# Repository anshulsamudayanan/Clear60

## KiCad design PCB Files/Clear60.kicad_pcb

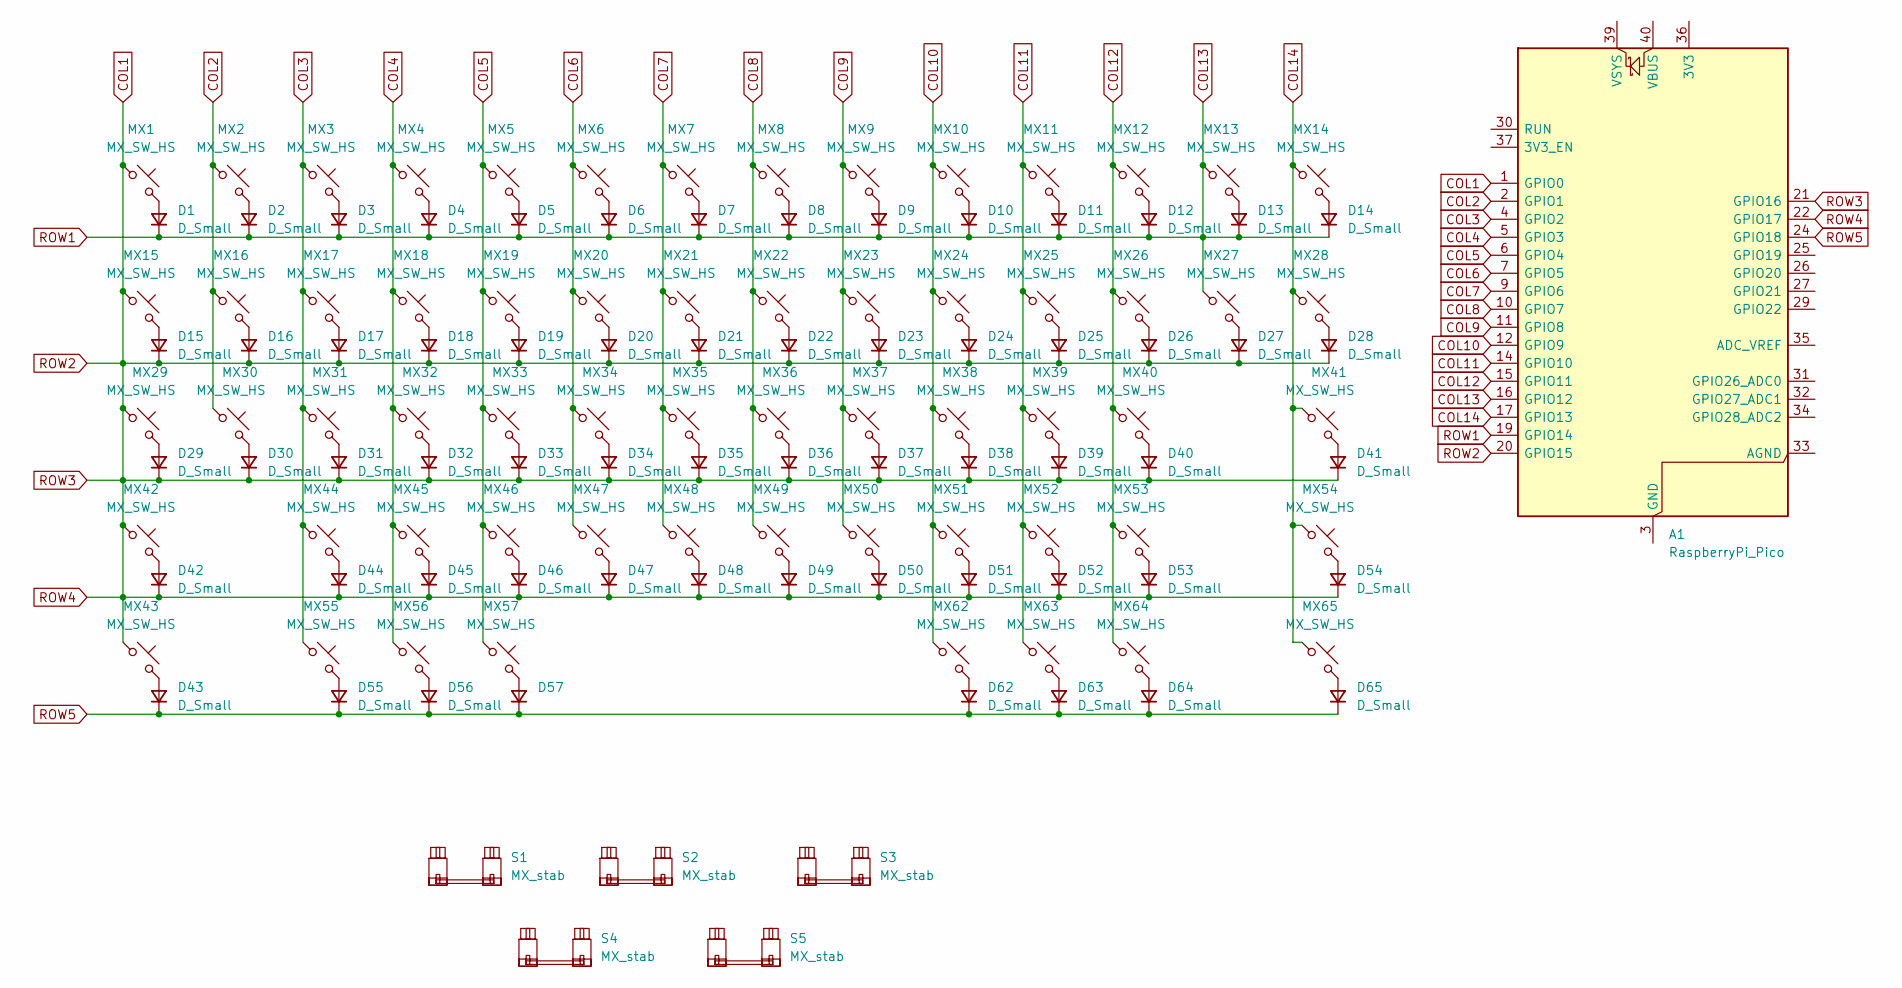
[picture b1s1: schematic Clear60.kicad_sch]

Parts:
A1: RaspberryPi_Pico; RaspberryPi_Pico_Common_Unspecified
D1, D2, D3, D4, D5, D6, D7, D8, D9, D10, D11, D12, D13, D14, D15, D16, D17, D18, D19, D20, D21, D22, D23, D24, D25, D26, D27, D28, D29, D30, D31, D32, D33, D34, D35, D36, D37, D38, D39, D40, D41, D42, D43, D44, D45, D46, D47, D48, D49, D50, D51, D52, D53, D54, D55, D56, D57, D62, D63, D64, D65: D_Small; D_SOD-123
MX1, MX2, MX3, MX4, MX5, MX6, MX7, MX8, MX9, MX10, MX11, MX12, MX13, MX14, MX16, MX17, MX18, MX19, MX20, MX21, MX22, MX23, MX24, MX25, MX26, MX27, MX30, MX31, MX32, MX33, MX34, MX35, MX36, MX37, MX38, MX39, MX40, MX41, MX42, MX44, MX45, MX46, MX47, MX48, MX49, MX50, MX51, MX52, MX53, MX54, MX57: MX_SW_HS; SW_MX_HS_CPG151101S11_1u
MX15, MX28: MX_SW_HS; SW_MX_HS_CPG151101S11_1.5u
MX29: MX_SW_HS; SW_MX_HS_CPG151101S11_1.75u
MX43, MX55, MX56, MX62, MX63, MX64, MX65: MX_SW_HS; SW_MX_HS_CPG151101S11_1.25u
S1, S3: MX_stab; STAB_MX_P_2.25u
S2: MX_stab; STAB_MX_P_2u
S4: MX_stab; STAB_MX_P_2.75u
S5: MX_stab; STAB_MX_P_6.25u

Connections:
COL1: A1.1 (GPIO0), A1.20 (GPIO15), A1.21 (GPIO16), A1.22 (GPIO17), D15.1 (K), D16.1 (K), D17.1 (K), D18.1 (K), D19.1 (K), D20.1 (K), D21.1 (K), D22.1 (K), D23.1 (K), D24.1 (K), D25.1 (K), D26.1 (K), D27.1 (K), D28.1 (K), D29.1 (K), D30.1 (K), D31.1 (K), D32.1 (K), D33.1 (K), D34.1 (K), D35.1 (K), D36.1 (K), D37.1 (K), D38.1 (K), D39.1 (K), D40.1 (K), D41.1 (K), D42.1 (K), D44.1 (K), D45.1 (K), D46.1 (K), D47.1 (K), D48.1 (K), D49.1 (K), D50.1 (K), D51.1 (K), D52.1 (K), D53.1 (K), D54.1 (K), MX1.1, MX15.1, MX29.1, MX42.1, MX43.1
COL2: A1.2 (GPIO1), MX2.1, MX16.1, MX30.1
COL3: A1.4 (GPIO2), MX3.1, MX17.1, MX31.1, MX44.1, MX55.1
COL4: A1.5 (GPIO3), MX4.1, MX18.1, MX32.1, MX45.1, MX56.1
COL5: A1.6 (GPIO4), MX5.1, MX19.1, MX33.1, MX46.1, MX57.1
COL6: A1.7 (GPIO5), MX6.1, MX20.1, MX34.1, MX47.1
COL7: A1.9 (GPIO6), MX7.1, MX21.1, MX35.1, MX48.1
COL8: A1.10 (GPIO7), MX8.1, MX22.1, MX36.1, MX49.1
COL9: A1.11 (GPIO8), MX9.1, MX23.1, MX37.1, MX50.1
COL10: A1.12 (GPIO9), MX10.1, MX24.1, MX38.1, MX51.1, MX62.1
COL11: A1.14 (GPIO10), MX11.1, MX25.1, MX39.1, MX52.1, MX63.1
COL12: A1.15 (GPIO11), MX12.1, MX26.1, MX40.1, MX53.1, MX64.1
COL13: A1.16 (GPIO12), A1.19 (GPIO14), D1.1 (K), D2.1 (K), D3.1 (K), D4.1 (K), D5.1 (K), D6.1 (K), D7.1 (K), D8.1 (K), D9.1 (K), D10.1 (K), D11.1 (K), D12.1 (K), D13.1 (K), D14.1 (K), MX13.1, MX27.1
COL14: A1.17 (GPIO13), MX14.1, MX28.1, MX41.1, MX54.1, MX65.1
unnamed: A1.3 (GND), A1.8 (GND), A1.13 (GND), A1.18 (GND), A1.23 (GND), A1.28 (GND), A1.38 (GND)
unnamed: D1.2 (A), MX1.2
unnamed: D2.2 (A), MX2.2
unnamed: D3.2 (A), MX3.2
unnamed: D4.2 (A), MX4.2
unnamed: D5.2 (A), MX5.2
unnamed: D6.2 (A), MX6.2
unnamed: D7.2 (A), MX7.2
unnamed: D8.2 (A), MX8.2
unnamed: D9.2 (A), MX9.2
unnamed: D10.2 (A), MX10.2
unnamed: D11.2 (A), MX11.2
unnamed: D12.2 (A), MX12.2
unnamed: D13.2 (A), MX13.2
unnamed: D14.2 (A), MX14.2
unnamed: D15.2 (A), MX15.2
unnamed: D16.2 (A), MX16.2
unnamed: D17.2 (A), MX17.2
unnamed: D18.2 (A), MX18.2
unnamed: D19.2 (A), MX19.2
unnamed: D20.2 (A), MX20.2
unnamed: D21.2 (A), MX21.2
unnamed: D22.2 (A), MX22.2
unnamed: D23.2 (A), MX23.2
unnamed: D24.2 (A), MX24.2
unnamed: D25.2 (A), MX25.2
unnamed: D26.2 (A), MX26.2
unnamed: D27.2 (A), MX27.2
unnamed: D28.2 (A), MX28.2
unnamed: D29.2 (A), MX29.2
unnamed: D30.2 (A), MX30.2
unnamed: D31.2 (A), MX31.2
unnamed: D32.2 (A), MX32.2
unnamed: D33.2 (A), MX33.2
unnamed: D34.2 (A), MX34.2
unnamed: D35.2 (A), MX35.2
unnamed: D36.2 (A), MX36.2
unnamed: D37.2 (A), MX37.2
unnamed: D38.2 (A), MX38.2
unnamed: D39.2 (A), MX39.2
unnamed: D40.2 (A), MX40.2
unnamed: D41.2 (A), MX41.2
unnamed: D42.2 (A), MX42.2
unnamed: D43.2 (A), MX43.2
unnamed: D44.2 (A), MX44.2
unnamed: D45.2 (A), MX45.2
unnamed: D46.2 (A), MX46.2
unnamed: D47.2 (A), MX47.2
unnamed: D48.2 (A), MX48.2
unnamed: D49.2 (A), MX49.2
unnamed: D50.2 (A), MX50.2
unnamed: D51.2 (A), MX51.2
unnamed: D52.2 (A), MX52.2
unnamed: D53.2 (A), MX53.2
unnamed: D54.2 (A), MX54.2
unnamed: D55.2 (A), MX55.2
unnamed: D56.2 (A), MX56.2
unnamed: D57.2 (A), MX57.2
unnamed: D62.2 (A), MX62.2
unnamed: D63.2 (A), MX63.2
unnamed: D64.2 (A), MX64.2
unnamed: D65.2 (A), MX65.2
ROW5: A1.24 (GPIO18), D43.1 (K), D55.1 (K), D56.1 (K), D57.1 (K), D62.1 (K), D63.1 (K), D64.1 (K), D65.1 (K)

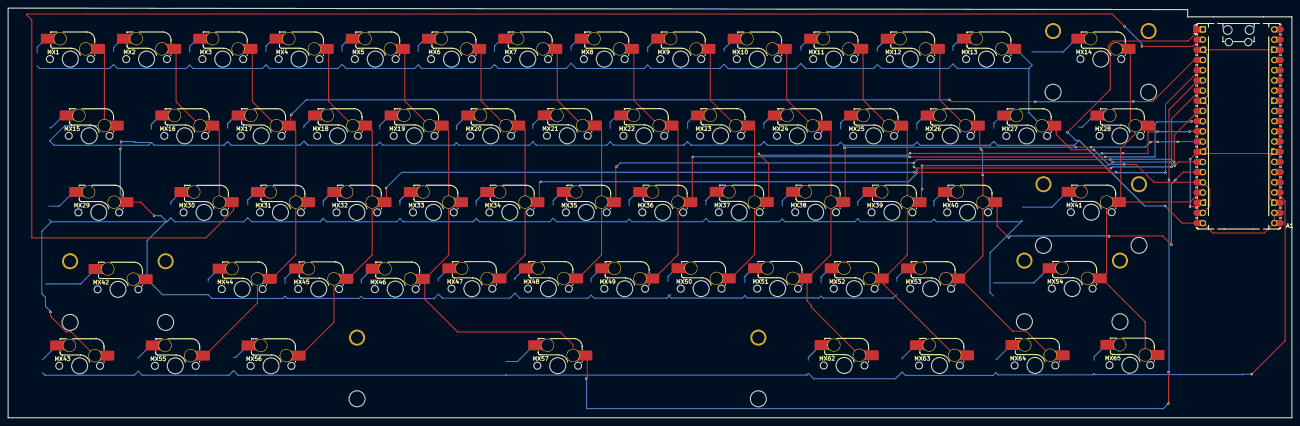
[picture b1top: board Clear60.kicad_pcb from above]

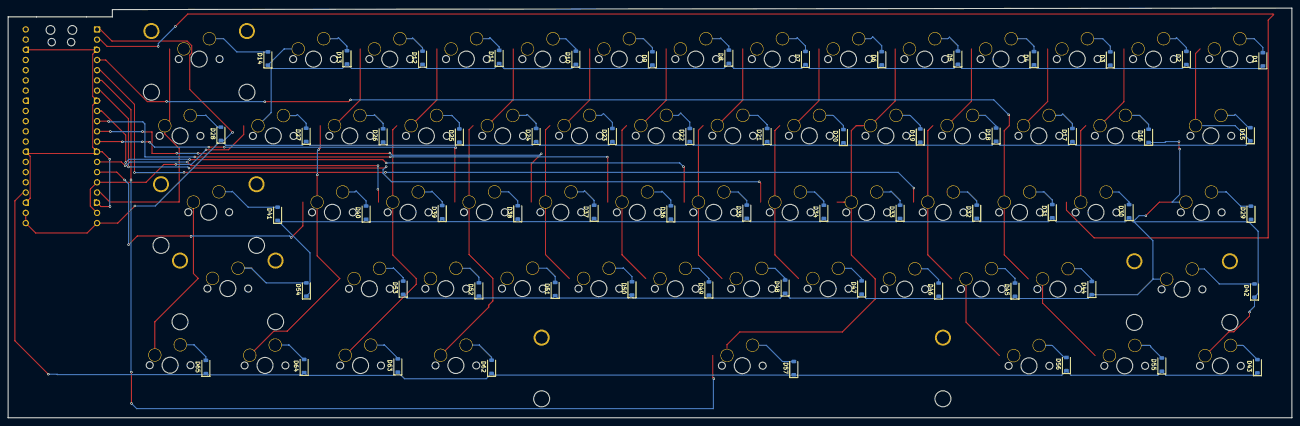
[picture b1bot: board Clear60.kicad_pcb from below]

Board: 2 copper layers, 319.9 x 102.1 mm, 128 parts (61 on the bottom side), 77 nets.

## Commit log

2025-12-20 Create temp
